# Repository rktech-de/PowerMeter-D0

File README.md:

# PowerMeter-D0
Read PowerMeter D0 (IR) interface with ESP8266 and transmit as MQTT

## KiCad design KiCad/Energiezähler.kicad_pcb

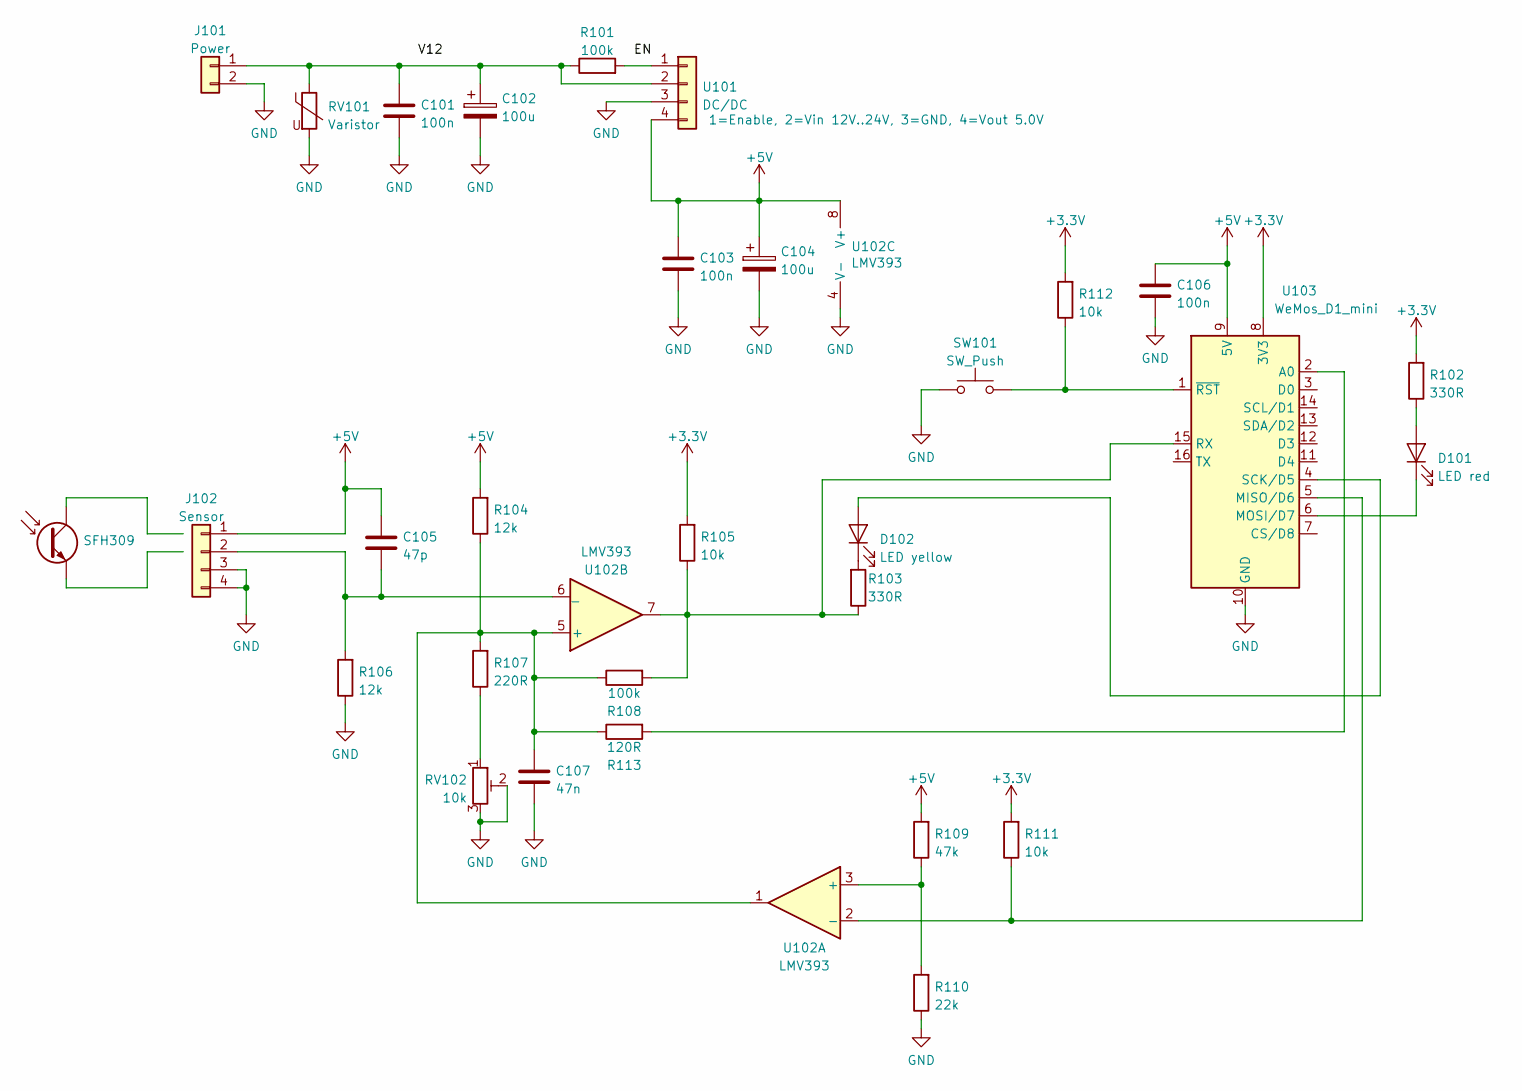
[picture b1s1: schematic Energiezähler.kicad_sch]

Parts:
C101, C103, C106: 100n; C_0805_2012Metric_Pad1.18x1.45mm_HandSolder
C102, C104: 100u; CP_Radial_D6.3mm_P2.50mm
C105: 47p; C_0805_2012Metric_Pad1.18x1.45mm_HandSolder
C107: 47n; C_0805_2012Metric_Pad1.18x1.45mm_HandSolder
D101: LED red; LED_D3.0mm
D102: LED yellow; LED_D3.0mm
J101: Power; PinHeader_1x02_P2.54mm_Vertical
J102: Sensor; PinHeader_1x04_P2.54mm_Vertical
Q0: SFH309
R101, R108: 100k; R_0805_2012Metric_Pad1.20x1.40mm_HandSolder
R102, R103: 330R; R_0805_2012Metric_Pad1.20x1.40mm_HandSolder
R104, R106: 12k; R_0805_2012Metric_Pad1.20x1.40mm_HandSolder
R105, R111, R112: 10k; R_0805_2012Metric_Pad1.20x1.40mm_HandSolder
R107: 220R; R_0805_2012Metric_Pad1.20x1.40mm_HandSolder
R109: 47k; R_0805_2012Metric_Pad1.20x1.40mm_HandSolder
R110: 22k; R_0805_2012Metric_Pad1.20x1.40mm_HandSolder
R113: 120R; R_0805_2012Metric_Pad1.20x1.40mm_HandSolder
RV101: Varistor; D_A-405_P12.70mm_Horizontal
RV102: 10k; Potentiometer_Bourns_3266W_Vertical
SW101: SW_Push; SW_Tactile_SPST_Angled_PTS645Vx58-2LFS
U101: DC/DC; PinHeader_1x04_P2.54mm_Vertical
U102: LMV393; DIP-8_W7.62mm
U103: WeMos_D1_mini; wemos-d1-mini-with-pin-header

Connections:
+3V3: R102.2, R105.2, R111.2, R112.2, U103.8 (3V3)
+5V: C103.1, C104.1, C105.1, C106.1, J102.1, R104.2, R109.2, U101.4, U102.8 (V+), U103.9 (5V)
GND: C101.2, C102.2, C103.2, C104.2, C106.2, C107.2, J101.2, J102.3, J102.4, R106.1, R110.1, RV101.2, RV102.2, RV102.3, SW101.1, U101.3, U102.4 (V-), U103.10 (GND)
unnamed: C101.1, C102.1, J101.1, R101.1, RV101.1, U101.2
unnamed: C105.2, J102.2, R106.2, U102.6 (_)
unnamed: C107.1, R104.1, R107.2, R108.1, R113.1, U102.1, U102.5 (+)
unnamed: D101.1 (K), U103.6 (MOSI/D7)
unnamed: D101.2 (A), R102.1
unnamed: D102.1 (K), R103.2
unnamed: D102.2 (A), U103.4 (SCK/D5)
unnamed: R101.2, U101.1
unnamed: R103.1, R105.1, R108.2, U102.7, U103.15 (RX)
unnamed: R107.1, RV102.1
unnamed: R109.1, R110.2, U102.3 (+)
unnamed: R111.1, U102.2 (-), U103.5 (MISO/D6)
unnamed: R112.1, SW101.2, U103.1 (~RST)
unnamed: R113.2, U103.2 (A0)

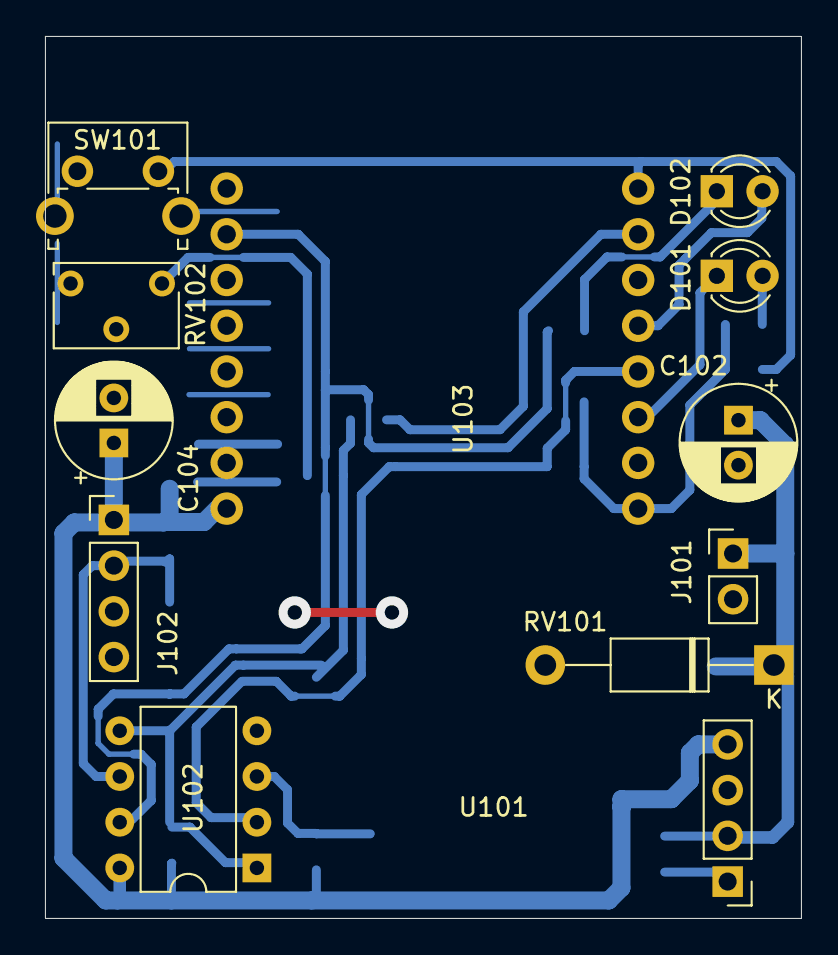
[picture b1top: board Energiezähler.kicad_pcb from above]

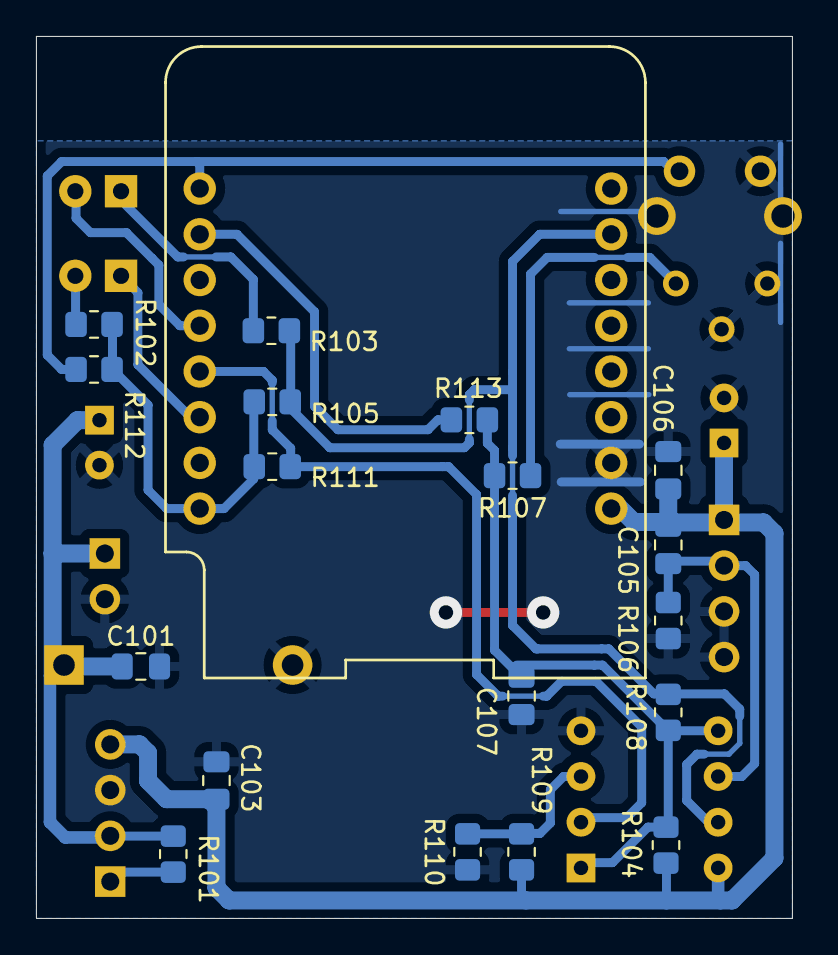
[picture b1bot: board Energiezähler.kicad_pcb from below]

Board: 2 copper layers, 42.0 x 49.0 mm, 30 parts (19 on the bottom side), 17 nets.

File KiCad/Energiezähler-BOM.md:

# Energiezähler.kicad_sch BOM

Mo 14 Nov 2022 20:32:45 CET

Generated from schematic by Eeschema 6.0.9-8da3e8f707~116~ubuntu20.04.1

**Component Count:** 31

| Refs | Qty | Component | Description |
| ----- | --- | ---- | ----------- |
| C101, C103, C106 | 3 | 100n | Unpolarized capacitor<br />Capacitor_SMD:C_0805_2012Metric_Pad1.18x1.45mm_HandSolder |
| C102, C104 | 2 | 100u | Polarized capacitor<br />Capacitor_THT:CP_Radial_D6.3mm_P2.50mm |
| C105 | 1 | 47p | Unpolarized capacitor<br />Capacitor_SMD:C_0805_2012Metric_Pad1.18x1.45mm_HandSolder |
| C107 | 1 | 47n | Unpolarized capacitor<br />Capacitor_SMD:C_0805_2012Metric_Pad1.18x1.45mm_HandSolder |
| D101 | 1 | LED red | Light emitting diode<br />LED_THT:LED_D3.0mm |
| D102 | 1 | LED yellow | Light emitting diode<br />LED_THT:LED_D3.0mm |
| J101 | 1 | Power | Generic connector, single row, 01x02, script generated (kicad-library-utils/schlib/autogen/connector/)<br />Connector_PinHeader_2.54mm:PinHeader_1x02_P2.54mm_Vertical |
| J102 | 1 | Sensor | Generic connector, single row, 01x04, script generated (kicad-library-utils/schlib/autogen/connector/)<br />Connector_PinHeader_2.54mm:PinHeader_1x04_P2.54mm_Vertical |
| Q0 | 1 | SFH309 | Phototransistor NPN<br />http://www.osram-os.com/Graphics/XPic2/00101811_0.pdf/SFH%20309,%20SFH%20309%20FA,%20Lead%20(Pb)%20Free%20Product%20-%20RoHS%20Compliant.pdf<br />LED_THT:LED_D3.0mm_Clear |
| R101, R108 | 2 | 100k | Resistor<br />Resistor_SMD:R_0805_2012Metric_Pad1.20x1.40mm_HandSolder |
| R102, R103 | 2 | 330R | Resistor<br />Resistor_SMD:R_0805_2012Metric_Pad1.20x1.40mm_HandSolder |
| R104, R106 | 2 | 12k | Resistor<br />Resistor_SMD:R_0805_2012Metric_Pad1.20x1.40mm_HandSolder |
| R105, R111, R112 | 3 | 10k | Resistor<br />Resistor_SMD:R_0805_2012Metric_Pad1.20x1.40mm_HandSolder |
| R107 | 1 | 220R | Resistor<br />Resistor_SMD:R_0805_2012Metric_Pad1.20x1.40mm_HandSolder |
| R109 | 1 | 47k | Resistor<br />Resistor_SMD:R_0805_2012Metric_Pad1.20x1.40mm_HandSolder |
| R110 | 1 | 22k | Resistor<br />Resistor_SMD:R_0805_2012Metric_Pad1.20x1.40mm_HandSolder |
| R113 | 1 | 120R | Resistor<br />Resistor_SMD:R_0805_2012Metric_Pad1.20x1.40mm_HandSolder |
| RV101 | 1 | Varistor | Voltage dependent resistor<br />Diode_THT:D_A-405_P12.70mm_Horizontal |
| RV102 | 1 | 10k | Trim-potentiometer<br />Potentiometer_THT:Potentiometer_Bourns_3266W_Vertical |
| SW101 | 1 | SW_Push | Push button switch, generic, two pins<br />Button_Switch_THT:SW_Tactile_SPST_Angled_PTS645Vx58-2LFS |
| U101 | 1 | DC/DC | Generic connector, single row, 01x04, script generated (kicad-library-utils/schlib/autogen/connector/)<br />https://www.amazon.de/PEMENOL-Einstellbar-Spannungwandler-St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 />Connector_PinHeader_2.54mm:PinHeader_1x04_P2.54mm_Vertical |
| U102 | 1 | LMV393 | http://www.ti.com/lit/ds/symlink/lmv331.pdf<br />Package_DIP:DIP-8_W7.62mm |
| U103 | 1 | WeMos_D1_mini | https://wiki.wemos.cc/products:d1:d1_mini#documentation<br />ESP8266:wemos-d1-mini-with-pin-header |

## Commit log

2022-11-14 Add ESP8266 code
2022-11-14 Add hardware data
2022-11-14 new hardware data
